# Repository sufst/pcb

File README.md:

# PCBs

## About
Central repository of all schematics and PCB design files.

| Folder     | Project                          | Project Code |
|------------|----------------------------------|--------------|
| ail        | Accumulator Indicator Light Logic| `ail`        |
| ail-led    | Accumulator Indicator Light Led  | `ail-led`    |
| batak      | Batak Game (non-car)             | `batak`      |
| break-light| Rear Break Light                 | `break-light`|
| bspd       | Brake System Plausibility Device | `bspd`       |
| can-node   | Voltage Reader and Broadcaster   | `can-node`   |
| curr-amp   | Current Sensor Amplifier         | `curr-amp`   |
| dash       | Dashboard                        | `dash`       |
| discharge  | Discharge Relay Breakout         | `discharge`  |
| hv-sense   | High Voltage Sense               | `hvs`        |
| latching   | Latch Circuit                    | `latching`   |
| loom*      | Loom Design                      | `loom`       |
| lvbms      | Low Voltage Battery Management System | `lvbms` |
| precharge  | Precharge Controller             | `precharge`  |
| segment    | Segment                          | `segment`    |
| telemetry  | On-Car Telemetry                 | `telemetry`  |
| test-rig   | PCB Test / Demo Rig              | `test`       |
| top-level* | Full Car Schematic               |              |
| trc        | TSAC Relay Controller            | `trc`        |
| tsal       | Tractive System Active Light     | `tsal`       |
| vcu        | Vehicle Control Unit             | `vcu`        |

We design our PCBs in KiCad (version 8+).

>*Moved to https://github.com/sufst/loom

## Version Control for KiCad Projects

### Why?
- Revert individual changes.
- Document development history via commits and GitHub issues.
- Easily view previous versions of designs.
- Manage shared library of components.

### Files

Files that should be in this repo, under version control:
- Project files (`.kicad_pro`).
- Schematic files (`.kicad_sch`).
- PCB files (`.kicad_pcb`).
- Custom footprints (`.kicad_mod`).
- Custom symbols (`.kicad_sym`).
- Footprint library tables (`fp-lib-table`).
- Symbol library tables (`sym-lib-table`).
- 3D models of components (`.step` files).
- Simulation code (e.g. `.asc` files from LTSpice).

Files that should never be in here:
- Exports such as BOMs, gerbers, netlists, renders, etc.
- Local project settings (`.kicad_prl`).
- Project backups (.zip files generated in `<project name>-backups`, `.bak` `.bck` `-bak` files).
- Cache files (`fp-info-cache`).

The `.gitignore` should prevent the addition of files we don't want to keep in here, but before you commit make sure to do a quick check of what is actually being added.

### Shared Resources

The `common` folder is used for resources which can be shared across multiple projects. This includes:

- Images (`images` subdirectory).
- 3D models (`step` subdirectory).
- Custom symbols (`sufst-lib.kicad_sym`).
- Custom footprints (`sufst-lib.pretty`).
- SUFST standard sheet layout (`sheet-layout.kicad_wks`).

> Note: Since projects were previously in their own individual repos, many designs still have their own libraries, step files, etc. These will gradually be migrated to the SUFST library.

### Library Paths
When you configure the library paths for a project (`sym-lib-table` and `fp-lib-table` data), make sure to always use a path relative to the project with the `${KIPRJMOD}` substitution.

- Correct: `${KIPRJMOD}/../common/sufst-lib.kicad_sym`
- Incorrect: `/Users/<your name>/Documents/sufst/pcb/common/sufst-lib.kicad_sym`

If an absolute path is used, when someone else opens the project that path will not exist and the library paths will not be valid. `-lib-table` files should never contain an absolute path.

### Git Limitations
It is not possible to resolve merge conflicts within individual design files, which is an unfortunate limitation of using `git` with KiCad. While KiCad files are in a text format, they aren't really designed to be edited manually. It is therefore *essential* that only one person is editing a particular file in a project at a time (including the shared library). Once someone starts working on a file, until it is merged into the `main` branch nobody else can edit that file. A good way to get round this is to use the "hierarchical sheets" feature to divide schematics into multiple files (if it can be done in a logical way).

## Releases

### Release Files
When a PCB is fabricated, a new 'release' for the given project should be 
created and stored within this repo in the `releases/<PROJECT NAME>` folder. 
This folder should contain the latest version (and ONLY the latest version) of
the following files:

1. Exported gerbers and drill files in a ZIP archive called `fabrication.zip`.
2. Schematic sheets as a PDF (`Schematic.pdf`).
3. Layout as a PDF in colour, with border and title block (`Layout.pdf`).
4. HTML iBOM created using the ["Interactive HTML BOM Plugin"](https://github.com/openscopeproject/InteractiveHtmlBom) (`ibom.html`).

Additionally, a file called `info` (no extension) should be created (if it 
doesn't already exist) containing release information in the following format:

```txt
version: <VERSION NUMBER>
date: <RELEASE DATE>
fabrication: <COMPANY>
```

Version numbers should be in the format `v1.0.1` and dates should be in the
format `YYYY-MM-DD`. For example:

```txt
version: v1.0.1
date: 2023-01-23
fabrication: JLCPCB
```

The release folder for a project should then have the following structure and 
file names:

```txt
<PROJECT NAME>
├── Layout.pdf
├── Schematic.pdf
├── fabrication.zip
├── ibom.html
└── info
```

When creating a new release, make sure to overwrite/replace all the existing 
files.

### Release Tag

The release commit should then be tagged with the following command:

```sh
git tag <PROJECT CODE>-<VERSION_NUMBER>
```

Tagging should be done **after** merging to `main`! Example command:

```sh
git tag segment-v1.0.1
```

To push tags to GitHub:

```sh
git push --tags
```

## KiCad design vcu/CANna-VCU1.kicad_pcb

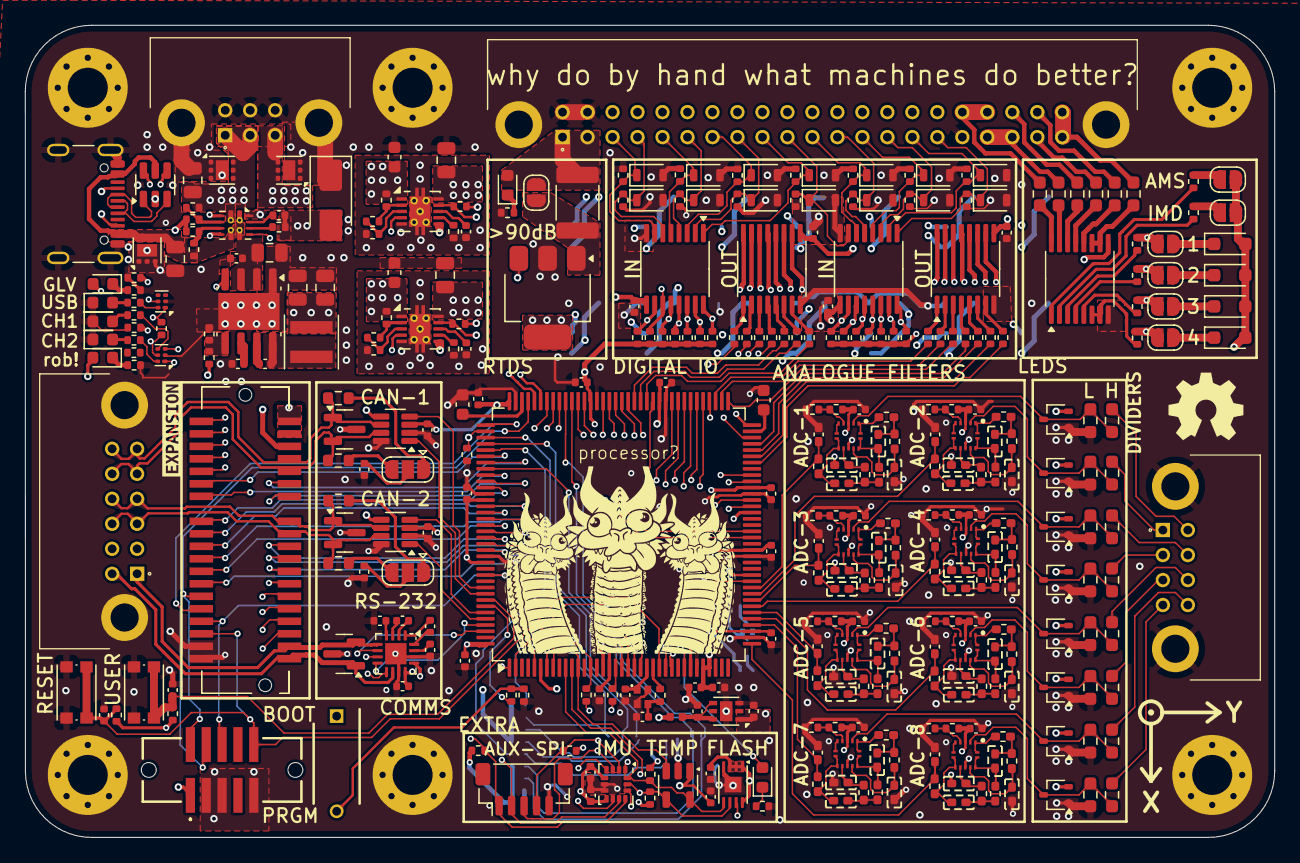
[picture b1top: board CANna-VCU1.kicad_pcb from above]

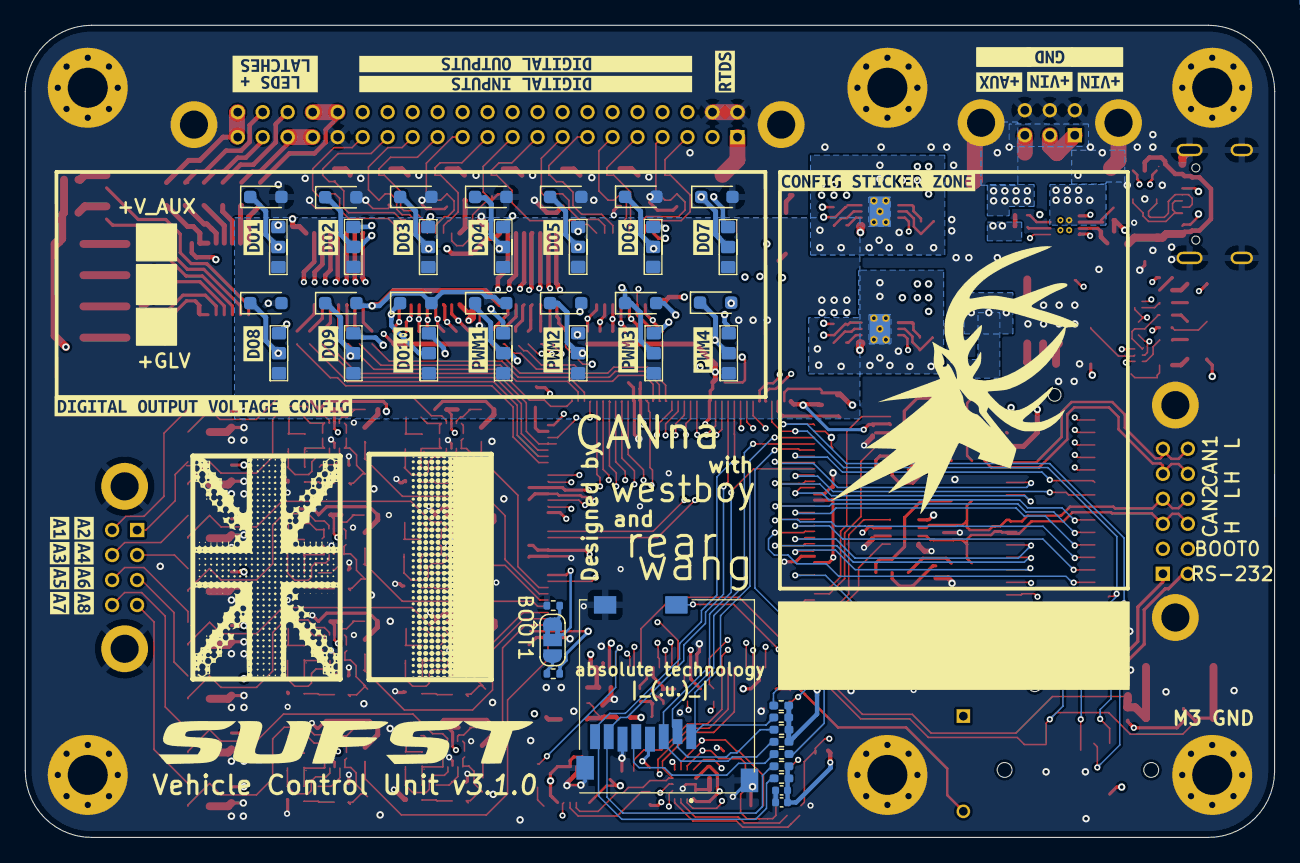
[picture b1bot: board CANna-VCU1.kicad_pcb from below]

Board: 6 copper layers, 100.0 x 65.0 mm, 442 parts (73 on the bottom side), 331 nets.

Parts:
C1, C5, C6, C8, C10, C11, C13, C14, C15, C16, C17, C19, C21, C22, C23, C31, C38, C77, C78, C79, C80, C81, C82, C83, C95, C96, C97, C98, C99, C100, C101, C104, C105, C106, C107, C108: 0.1uF; C_0402_1005Metric
C2: 10uF; C_0402_1005Metric
C3, C24, C36, C37, C39: 1uF; C_0402_1005Metric
C7, C9: 4.7pF; C_0402_1005Metric
C12: 4.7uF; C_0402_1005Metric
C18, C20: 2.2uF; C_0603_1608Metric
C25, C26, C32, C33, C34: 10uF; C_0805_2012Metric
C27, C28: 10nF; C_0402_1005Metric
C29, C30: 1uF; C_0603_1608Metric
C35: 220nF; C_0402_1005Metric
C40, C41: 22uF; C_0805_2012Metric
C42, C43, C44, C45, C46, C47, C48, C49, C50, C51, C52, C53, C54, C55, C56, C57, C58, C59, C60, C61, C62, C63, C64, C65, C66, C67, C68, C69: x; capacitor_0402_handsolder_nosilk
C70, C71, C72, C73, C74, C75, C76: x; C_0402_1005Metric_Pad0.74x0.62mm_HandSolder
C85, C89: 1nF; capacitor_0402_handsolder_nosilk
C86: 1.54nF; capacitor_0402_handsolder_nosilk
C90: 10.5nF; capacitor_0402_handsolder_nosilk
C92: 1nF; C_0402_1005Metric_Pad0.74x0.62mm_HandSolder
C102, C103: 4.7nF; C_0402_1005Metric
D1, D51: LED_BLUE; LED_0603_1608Metric
D2, D14, D33: LED_RED; LED_0603_1608Metric
D3: SS14; D_SMA
D4, D6: LED_GREEN; LED_0603_1608Metric
D7, D8, D9, D10, D11, D12, D13: BAT54SW,115; SOT-323_SC-70
D15, D16, D17, D18, D19, D20, D21, D22, D23, D24, D25, D26, D27, D28: TSD18DYFR; D_SOD-323_wide
D29, D30, D31, D32: NSR0340HT1G; D_SOD-323_HandSoldering
D34, D35, D36, D37, D38, D39, D40, D41, D42, D43, D44, D45, D46, D47: TSD18DYFR; D_SOD-323_HandSoldering
D48, D49, D50: NUP2105LT1G; SOT-23
FB1: 0; L_0402_1005Metric
H1, H2, H3, H4, H5, H6: MountingHole_Pad; MountingHole_3.2mm_M3_Pad_Via
J1: M80-5404242
J2: M80-5401242
J3: M80-5400842
J4: M80-5400642
J5: USB4105-GF-A; USB_C_Receptacle_GCT_USB4105-xx-A_16P_TopMnt_Horizontal
J6: MEC1-120-02-L-D-A-K-TR; MEC112002LDAKTR
J7: MEM2061-01-188-00-A; MEM20610118800A
J8: BM05B-SRSS-TB(LF)(SN); JST_SH_BM05B-SRSS-TB_1x05-1MP_P1.00mm_Vertical
J9: SHF-105-01-L-D-SM-LC; SHF10501LDSMLC
JP1: SolderJumper_3_Bridged12; SolderJumper-3_P1.3mm_Bridged2Bar12_RoundedPad1.0x1.5mm
JP2, JP3, JP4, JP5, JP6, JP7, JP8: SolderJumper_2_Open; SolderJumper-2_P1.3mm_Open_RoundedPad1.0x1.5mm
JP9, JP10: SolderJumper_3_Open; SolderJumper-3_P1.3mm_Open_RoundedPad1.0x1.5mm
L1: XFL4020-222MEC; L_Coilcraft_XxL4020
MP1: BAT54SW,115; SOT-323_SC-70
R1: 1k; R_0402_1005Metric_Pad0.72x0.64mm_HandSolder
R2, R3, R6, R7, R8: 47k; R_0402_1005Metric_Pad0.72x0.64mm_HandSolder
R4, R5, R32, R34: 5.1k; R_0402_1005Metric
R9: 22R; R_0402_1005Metric_Pad0.72x0.64mm_HandSolder
R10, R17, R18, R187, R188: 10k; R_0402_1005Metric
R11, R12: 47k; R_0402_1005Metric
R13, R16, R39, R41, R42, R45: 100k; R_0402_1005Metric
R14, R193: 560R; R_0402_1005Metric
R15: 1.3k; R_0402_1005Metric
R19, R20, R38, R43: 1.5k; R_0402_1005Metric
R21, R22: 2.2k; R_0402_1005Metric
R23, R180: 3k; R_0402_1005Metric
R24, R27: 300k; R_0402_1005Metric
R25, R28: 82k; R_0402_1005Metric
R26, R29: 30k; R_0402_1005Metric
R30, R35: 7.5k; R_0402_1005Metric
R31: 22k; R_0402_1005Metric
R33: 150k; R_0402_1005Metric
R37: 20k; R_0402_1005Metric
R40: 56k; R_0402_1005Metric
R46: 43.2k; R_0402_1005Metric
R49, R50, R51, R52, R53, R54, R55, R56, R57, R58, R59, R60, R61, R62: x; R_0603_1608Metric_Pad0.98x0.95mm_HandSolder
R63, R64, R65, R66, R67, R68, R69, R70, R71, R72, R73, R74, R75, R76, R77, R78, R79, R80, R81, R82, R83, R84, R85, R86, R87, R88, R89, R90, R91, R92, R93, R94, R95, R96, R97: x; R_0402_1005Metric_Pad0.72x0.64mm_HandSolder
R98, R99, R100, R101, R102, R103, R104, R105, R106, R107, R108, R109, R110, R111, R130, R131, R132, R133, R134, R135, R136, R137, R138, R139, R140, R141, R142, R143: x; R_0402_1005Metric
R112: 306k; R_0603_1608Metric_Pad0.98x0.95mm_HandSolder
R113: 214.5k; R_0603_1608Metric_Pad0.98x0.95mm_HandSolder
R116: 2.37k; R_0402_1005Metric_Pad0.72x0.64mm_HandSolder
R117: 2.8k; R_0402_1005Metric_Pad0.72x0.64mm_HandSolder
R122: 931R; R_0402_1005Metric_Pad0.72x0.64mm_HandSolder
R123: 1.05k; R_0402_1005Metric_Pad0.72x0.64mm_HandSolder
R126: 3.16k; R_0402_1005Metric_Pad0.72x0.64mm_HandSolder
R128, R129: 250k; R_0402_1005Metric
R144, R145, R146, R147, R148, R149, R150, R151, R152, R153, R154, R155, R156, R157: 1k; R_0402_1005Metric
R158, R159, R160, R161, R162, R163, R164, R165, R166, R167, R168, R169, R170, R171, R172, R174, R175, R176, R177, R178, R179: 0; R_0402_1005Metric
R173: 30; R_1812_4532Metric_Pad1.30x3.40mm_HandSolder
R181, R182, R183, R184, R185, R186: 0; R_0603_1608Metric_Pad0.98x0.95mm_HandSolder
R189, R190, R191, R192: 60R; R_0603_1608Metric
SW1, SW3: KMR241G LFS; SW_Push_1P1T_NO_CK_KMR2
SW2: A6T-1102; A6T-1101
U1: USBLC6-2SC6; SOT-23-6
U2: M24256E-FMC6TG; WFDFPN-8-1EP_3x2mm_P0.5mm_EP1.25x1.35mm
U3: ISM330DHCXTR; LGA-14_3x2.5mm_P0.5mm_LayoutBorder3x4y
U4: MCP9800A5T-M/OT; SOT-23-5
U5: STM32F746ZGT6; LQFP-144_20x20mm_P0.5mm
U6, U8: TVS1800DRVR; WSON-6-1EP_2x2mm_P0.65mm_EP1x1.6mm
U7: TVS0500DRVR; WSON-6-1EP_2x2mm_P0.65mm_EP1x1.6mm
U9, U10: TPS26625DRCR; VSON-10-1EP_3x3mm_P0.5mm_EP1.65x2.4mm_ThermalVias
U11: TPS2121RUXR; Texas_VQFN-HR-12_2x2.5mm_P0.5mm_ThermalVias
U12: NCV8730BMTW330TBG; DFN-6-1EP_2x2mm_P0.65mm_EP1x1.6mm
U13: LMR33630BDDAR; Texas_R-PDSO-G8_EP2.95x4.9mm_Mask2.4x3.1mm
U14, U15: SN74LVC2G17DRYR; Texas_USON-6_1x1.45mm_P0.5mm_SMD
U16, U17, U18, U19, U20, U21, U22, U23: TLV9104IRUCR
U25, U26, U28, U29, U30: TPL7407LPWR; TSSOP-16_4.4x5mm_P0.65mm
U27: ISP452HUMA1; SOT-223
U31, U32, U33, U34, U35, U36, U37, U38, U39, U40, U41, U42, U43, U44: SUFST_2x_Resistor_Selector_0603
U46, U47: TCAN3403DDFRQ1; SOT-23-8
U48: TRS3221EIRGTR; QFN-16-1EP_3x3mm_P0.5mm_EP1.7x1.7mm
Y1: ECS-250-10-47Q-CES-TR; Resonator_SMD_ECS_ECX-1247Q_1.6x1.2x0.3mm
kibuzzard-697BD61C: G***; kibuzzard-697BD61C
kibuzzard-6946D805: G***; kibuzzard-6946D805
kibuzzard-6946DF4F: G***; kibuzzard-6946DF4F
kibuzzard-6946DFE5: G***; kibuzzard-6946DFE5
kibuzzard-6946DFEA: G***; kibuzzard-6946DFEA
kibuzzard-6946DFF1: G***; kibuzzard-6946DFF1
kibuzzard-6946E0D2: G***; kibuzzard-6946E0D2
kibuzzard-6946E03E: G***; kibuzzard-6946E03E
kibuzzard-6946E12C: G***; kibuzzard-6946E12C
kibuzzard-6946E15A: G***; kibuzzard-6946E15A
kibuzzard-6946E16B: G***; kibuzzard-6946E16B
kibuzzard-6946E17E: G***; kibuzzard-6946E17E
kibuzzard-6946E038: G***; kibuzzard-6946E038
kibuzzard-6946E049: G***; kibuzzard-6946E049
kibuzzard-6946E137: G***; kibuzzard-6946E137
kibuzzard-6946E173: G***; kibuzzard-6946E173
kibuzzard-6955C1D0: G***; kibuzzard-6955C1D0
kibuzzard-6955C37E: G***; kibuzzard-6955C37E
kibuzzard-6955C320: G***; kibuzzard-6955C320
kibuzzard-6955C357: G***; kibuzzard-6955C357
kibuzzard-69488B9C, kibuzzard-69488B9C#2: G***; kibuzzard-69488B9C
kibuzzard-69488E03: G***; kibuzzard-69488E03
kibuzzard-694886AE: G***; kibuzzard-694886AE
kibuzzard-694896AB: G***; kibuzzard-694896AB
kibuzzard-694896B2: G***; kibuzzard-694896B2
kibuzzard-694896BE: G***; kibuzzard-694896BE
kibuzzard-694896C3: G***; kibuzzard-694896C3
kibuzzard-694896CA: G***; kibuzzard-694896CA
kibuzzard-694896CF: G***; kibuzzard-694896CF
kibuzzard-6944371B: G***; kibuzzard-6944371B
kibuzzard-69489640: G***; kibuzzard-69489640
kibuzzard-69489657: G***; kibuzzard-69489657

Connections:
+3V3: C1.2, C2.1, C5.2, C6.2, C8.1, C11.1, C12.1, C13.1, C14.1, C15.1, C16.1, C17.1, C19.1, C21.1, C22.1, C40.1, C41.1, C100.2, C101.2, C105.2, J2.8, J6.6, J7.P4 (VDD), J9.1 (VTref), L1.2, R1.2, R2.2, R3.2, R6.2, R7.2, R8.2, R10.1, R11.2, R12.2, R16.2, R21.2, R22.2, R45.2, R144.2, R145.2, R146.2, R147.2, R148.2, R149.2, R150.2, R151.2, R152.2, R153.2, R154.2, R155.2, R156.2, R157.2, R187.2, SW2.1 (A), U2.1 (E0), U2.2 (E1), U2.3 (E2), U2.8 (VCC), U3.5 (VDDIO), U3.8 (VDD), U4.1 (V_{DD}), U5.6 (VBAT), U5.17 (VDD), U5.30 (VDD), U5.39 (VDD), U5.52 (VDD), U5.62 (VDD), U5.72 (VDD), U5.84 (VDD), U5.95 (VDDUSB), U5.108 (VDD), U5.121 (VDD), U5.131 (VDD), U5.144 (VDD), U46.3 (VCC), U46.5 (SHDN), U47.3 (VCC), U47.5 (SHDN), U48.12 (VCC)
+3V3A: C23.1, C24.1, C39.1, C77.2, C78.2, C79.2, C80.2, C81.2, C82.2, C83.2, C95.2, D7.2 (K), D8.2 (K), D9.2 (K), D10.2 (K), D11.2 (K), D12.2 (K), D13.2 (K), MP1.2 (K), R37.2, R39.2, R41.2, R42.2, R98.2, R100.2, R102.2, R104.2, R106.2, R108.2, R110.2, R128.2, U5.32 (VREF+), U5.33 (VDDA), U12.1 (OUT), U14.5 (V_{CC}), U15.5 (V_{CC}), U16.3 (V+), U17.3 (V+), U18.3 (V+), U19.3 (V+), U20.3 (V+), U21.3 (V+), U22.3 (V+), U23.3 (V+)
+5V_USB: C25.1, J5.A4 (VBUS), J5.A9 (VBUS), J5.B4 (VBUS), J5.B9 (VBUS), R31.1, U1.5 (VBUS), U7.4 (IN), U7.5 (IN), U7.6 (IN), U11.7 (IN1)
+VIN: C26.1, C29.1, C96.1, C97.1, C98.2, C99.2, D2.2 (A), J4.1, J4.2, J6.2, R24.1, R33.1, U6.4 (IN), U6.5 (IN), U6.6 (IN), U9.1 (IN), U11.2 (IN2), U25.9 (VCC), U26.9 (VCC), U28.9 (VCC), U29.9 (VCC), U30.9 (COM)
+V_AUX: C30.1, J4.3, R27.1, U8.4 (IN), U8.5 (IN), U8.6 (IN), U10.1 (IN)
+V_CH1: C33.1, U9.10 (OUT), U27.4 (Vbb), U31.2, U32.2, U33.2, U34.2, U35.2, U36.2, U37.2, U38.2, U39.2, U40.2, U41.2, U42.2, U43.2, U44.2
+V_CH2: C32.1, U10.10 (OUT), U31.1, U32.1, U33.1, U34.1, U35.1, U36.1, U37.1, U38.1, U39.1, U40.1, U41.1, U42.1, U43.1, U44.1
/A1_IN: J3.5, R112.1
/A2_IN: J3.1, R52.1
/A3_IN: J3.6, R53.1
/A4_IN: J3.2, R54.1
/A5_IN: J3.7, R55.1
/A6_IN: J3.3, R49.1
/A7_IN: J3.8, R50.1
/A8_IN: J3.4, R51.1
/ADC/A1_MCU: C92.1, R126.1, U5.46 (PB0)
/ADC/A2_MCU: C73.1, R94.1, U5.45 (PC5)
/ADC/A3_MCU: C74.1, R95.1, U5.44 (PC4)
/ADC/A4_MCU: C75.1, R96.1, U5.43 (PA7)
/ADC/A5_MCU: C76.1, R97.1, U5.42 (PA6)
/ADC/A6_MCU: C70.1, R91.1, U5.41 (PA5)
/ADC/A7_MCU: C71.1, R92.1, U5.40 (PA4)
/ADC/A8_MCU: C72.1, R93.1, U5.37 (PA3)
/BOOT_SW: J2.2, R17.1, R18.2, SW2.2 (B)
/CAN1+: D48.2 (K), J2.5, J2.11, J6.10, R189.2, U46.7 (CANH)
/CAN1-: D48.1 (K), J2.6, J2.12, J6.8, R190.1, U46.6 (CANL)
/CAN2+: D49.2 (K), J2.3, J2.9, J6.20, R191.2, U47.7 (CANH)
/CAN2-: D49.1 (K), J2.4, J2.10, J6.18, R192.1, U47.6 (CANL)
/CAN/CAN1_RX: U5.135 (PB5), U46.4 (RXD)
/CAN/CAN1_TX: U5.136 (PB6), U46.1 (TXD)
/CAN/CAN2_RX: U5.139 (PB8), U47.4 (RXD)
/CAN/CAN2_TX: U5.140 (PB9), U47.1 (TXD)
/CAN/RS232_BAD: U5.5 (PE6), U48.7 (~INVALID)
/CAN/RS232_FOFF: U5.7 (PC13), U48.13 (~FORCEOFF)
/CAN/RS232_FON: U5.8 (PC14), U48.9 (FORCEON)
/CAN/UART0_RX: U5.141 (PE0), U48.8 (DIN)
/CAN/UART0_TX: U5.142 (PE1), U48.6 (ROUT)
/DI_1: D27.1 (K), J1.3, R142.1, U25.7 (A7)
/DI_2: D25.1 (K), J1.4, R140.1, U25.6 (A6)
/DI_3: D23.1 (K), J1.5, R138.1, U25.5 (A5)
/DI_4: D21.1 (K), J1.6, R136.1, U25.4 (A4)
/DI_5: D19.1 (K), J1.7, R134.1, U25.3 (A3)
/DI_6: D17.1 (K), J1.8, R132.1, U25.2 (A2)
/DI_7: D15.1 (K), J1.9, R130.1, U25.1 (A1)
/DI_8: D28.1 (K), J1.10, R143.1, U26.7 (A7)
/DI_9: D26.1 (K), J1.11, R141.1, U26.6 (A6)
/DI_10: D24.1 (K), J1.12, R139.1, U26.5 (A5)
/DI_11: D22.1 (K), J1.13, R137.1, U26.4 (A4)
/DI_12: D20.1 (K), J1.14, R135.1, U26.3 (A3)
/DI_13: D18.1 (K), J1.15, R133.1, U26.2 (A2)
/DI_14: D16.1 (K), J1.16, R131.1, U26.1 (A1)
/DO_1: D34.1 (K), J1.37, U29.10 (Y7), U32.3
/DO_2: D36.1 (K), J1.36, U29.11 (Y6), U34.3
/DO_3: D38.1 (K), J1.35, U29.12 (Y5), U36.3
/DO_4: D40.1 (K), J1.34, U29.13 (Y4), U38.3
/DO_5: D42.1 (K), J1.33, U29.14 (Y3), U40.3
/DO_6: D44.1 (K), J1.32, U29.15 (Y2), U42.3
/DO_7: D46.1 (K), J1.31, U29.16 (Y1), U44.3
/DO_8: D35.1 (K), J1.30, U28.10 (Y7), U31.3
/DO_9: D37.1 (K), J1.29, U28.11 (Y6), U33.3
/DO_10: D39.1 (K), J1.28, U28.12 (Y5), U35.3
/HSIO/CHECK_LED: D29.2 (A), D30.2 (A), D31.2 (A), D32.2 (A), JP2.1 (A), JP3.1 (A), U5.58 (PE7)
/HSIO/LATCH_1: R181.1, U30.16 (OUT1)
/HSIO/LATCH_2: R182.1, U30.15 (OUT2)
/HSIO/LSDI_1: R157.1, U5.97 (PC7), U25.10 (Y7)
/HSIO/LSDI_2: R155.1, U5.96 (PC6), U25.11 (Y6)
/HSIO/LSDI_3: R153.1, U5.93 (PG8), U25.12 (Y5)
/HSIO/LSDI_4: R151.1, U5.92 (PG7), U25.13 (Y4)
/HSIO/LSDI_5: R149.1, U5.91 (PG6), U25.14 (Y3)
/HSIO/LSDI_6: R147.1, U5.90 (PG5), U25.15 (Y2)
/HSIO/LSDI_7: R145.1, U5.89 (PG4), U25.16 (Y1)
/HSIO/LSDI_8: R156.1, U5.85 (PD14), U26.10 (Y7)
/HSIO/LSDI_9: R154.1, U5.82 (PD13), U26.11 (Y6)
/HSIO/LSDI_10: R152.1, U5.81 (PD12), U26.12 (Y5)
/HSIO/LSDI_11: R150.1, U5.80 (PD11), U26.13 (Y4)
/HSIO/LSDI_12: R148.1, U5.79 (PD10), U26.14 (Y3)
/HSIO/LSDI_13: R146.1, U5.78 (PD9), U26.15 (Y2)
/HSIO/LSDI_14: R144.1, U5.77 (PD8), U26.16 (Y1)
/HSIO/LSDO_1: R172.2, U5.66 (PE13)
/HSIO/LSDO_2: R171.2, U5.67 (PE14)
/HSIO/LSDO_3: R170.2, U5.68 (PE15)
/HSIO/LSDO_4: R169.2, U5.69 (PB10)
/HSIO/LSDO_5: R168.2, U5.73 (PB12)
/HSIO/LSDO_6: R167.2, U5.74 (PB13)
/HSIO/LSDO_7: R166.2, U5.75 (PB14)
/HSIO/LSDO_8: R165.2, U5.86 (PD15)
/HSIO/LSDO_9: R164.2, U5.87 (PG2)
/HSIO/LSDO_10: R163.2, U5.88 (PG3)
/HSIO/LSDO_PWM1: R162.2, U5.70 (PB11)
/HSIO/LSDO_PWM2: R161.2, U5.76 (PB15)
/HSIO/LSDO_PWM3: R160.2, U5.47 (PB1)
/HSIO/LSDO_PWM4: R159.2, U5.19 (PF7)
/HSIO/LSD_RTDS: R158.1, U5.18 (PF6)
/HSIO/LS_LED_1: JP4.2 (B), R176.2, U5.64 (PE11)
/HSIO/LS_LED_2: JP5.2 (B), R177.2, U5.63 (PE10)
/HSIO/LS_LED_3: JP6.2 (B), R178.2, U5.60 (PE9)
/HSIO/LS_LED_4: JP7.2 (B), R179.2, U5.59 (PE8)
/LATCH_1: J1.38, J1.39, R181.2
/LATCH_2: J1.18, J1.19, R182.2
/LS_LED_1: J1.40, R183.2
/LS_LED_2: J1.20, R184.2
/LS_LED_3: J1.41, R185.2
/LS_LED_4: J1.21, J1.42, R186.2
/MCU/AUX_ENAB: J6.34, J8.2, U3.10 (OCS_AUX)
/MCU/AUX_SCK: J6.32, J8.3, U3.3 (SCx)
/MCU/AUX_SDI: J6.30, J8.4, R11.1, U3.2 (SDx)
/MCU/AUX_SDO: J6.36, J8.1, R12.1, U3.11 (SDO_AUX)
/MCU/BOOT0: R18.1, U5.138 (BOOT0)
/MCU/BOOT1: JP1.2 (C), U5.48 (PB2)
/MCU/EEPROM_WC: U2.7 (WC), U5.27 (PC1)
/MCU/I2C0_SCL: R22.1, U2.6 (SCL), U3.13 (SCL), U4.4 (SCLK), U5.11 (PF1)
/MCU/I2C0_SDA: R21.1, U2.5 (SDA), U3.14 (SDA), U4.5 (SDA), U5.10 (PF0)
/MCU/I2C1_SCL: J6.3, U5.54 (PF14)
/MCU/I2C1_SDA: J6.1, U5.55 (PF15)
/MCU/IMU_ADDR: U3.1 (SDO/SA0), U5.22 (PF10)
/MCU/IMU_INTR1: U3.4 (INT1), U5.20 (PF8)
/MCU/IMU_INTR2: U3.9 (INT2), U5.21 (PF9)
/MCU/IMU_MODE: U3.12 (CS), U5.26 (PC0)
/MCU/OSC_IN: C9.1, U5.23 (PH0), Y1.1
/MCU/OSC_OUT: R15.1, U5.24 (PH1)
/MCU/PG_3V3: R42.1, U5.14 (PF4), U13.4 (PG)
/MCU/SD_CARD_DETECT: J7.CD1 (DET_A), R1.1, U5.2 (PE3)
/MCU/SD_CK: R9.2, U5.113 (PC12)
/MCU/SD_CMD: J7.P3 (CMD), R8.1, U5.116 (PD2)
/MCU/SD_D0: J7.P7 (DAT0), R2.1, U5.98 (PC8)
/MCU/SD_D1: J7.P8 (DAT1), R3.1, U5.99 (PC9)
/MCU/SD_D2: J7.P1 (DAT2), R6.1, U5.111 (PC10)
/MCU/SD_D3: J7.P2 (DAT3/CD), R7.1, U5.112 (PC11)
/MCU/SPI_MISO: J6.22, U5.127 (PG12)
/MCU/SPI_MOSI: J6.26, U5.129 (PG14)
/MCU/SPI_SCK: J6.24, U5.128 (PG13)
/MCU/SWCLK: J6.31, J9.4 (SWCLK/TCK), U5.109 (PA14)
/MCU/SWDIO: J6.29, J9.2 (SWDIO/TMS), U5.105 (PA13)
/MCU/SWO: J6.33, J9.6 (SWO/TDO), U5.133 (PB3)
/MCU/TOO_HOT: J6.28, U4.3 (ALERT), U5.12 (PF2)
/MCU/USART1_CK: J6.5, U5.100 (PA8)
/MCU/USART1_RX: J6.9, U5.102 (PA10)
/MCU/USART1_TX: J6.7, U5.101 (PA9)
/MCU/USB_D+: U1.4 (I/O2), U5.104 (PA12)
/MCU/USB_D-: U1.6 (I/O1), U5.103 (PA11)
/MCU/USB_UN_D+: J5.A6 (D+), J5.B6 (D+), U1.3 (I/O2)
/MCU/USB_UN_D-: J5.A7 (D-), J5.B7 (D-), U1.1 (I/O1)
/MCU/XP_GP_1: J6.11, U5.114 (PD0)
/MCU/XP_GP_2: J6.12, U5.115 (PD1)
/MCU/XP_GP_3: J6.13, U5.117 (PD3)
/MCU/XP_GP_4: J6.14, U5.118 (PD4)
/MCU/XP_GP_5: J6.17, U5.119 (PD5)
/MCU/XP_GP_6: J6.19, U5.122 (PD6)
/MCU/XP_GP_7: J6.21, U5.123 (PD7)
/MCU/XP_GP_8: J6.23, U5.124 (PG9)
/MCU/XP_GP_9: J6.25, U5.125 (PG10)
/MCU/XP_GP_10: J6.27, U5.126 (PG11)
/MCU/button: C3.2, R10.2, SW1.1, U5.137 (PB7)
/MCU/nRST: C10.2, J6.35, J9.10 (~RESET), R16.1, SW3.1, U5.25 (NRST)
/MCU/rob_led!: D1.2 (A), U5.1 (PE2)
/MCU/spare_led: D51.2 (A), U5.29 (PC3)
/MCU/~KILL: R13.2, U5.110 (PA15), U9.4 (~(SHDN)), U10.4 (~(SHDN))
/PWM1: D41.1 (K), J1.27, U28.13 (Y4), U37.3
/PWM2: D43.1 (K), J1.26, U28.14 (Y3), U39.3
/PWM3: D45.1 (K), J1.25, U28.15 (Y2), U41.3
/PWM4: D47.1 (K), J1.24, U28.16 (Y1), U43.3
/Power/FB1: R45.1, R46.2, U13.5 (FB)
/Power/MUX: R37.1, U11.9 (ST), U15.1 (1A)
/Power/SW: C38.2, L1.1, U13.8 (SW)
/Power/~FAULT_CH1: R39.1, U9.9 (~(FLT)), U14.3 (2A)
/Power/~FAULT_CH2: R41.1, U10.9 (~(FLT)), U14.1 (1A)
/RS232_RX: D50.2 (K), J2.1, J6.38, U48.5 (RIN)
/RS232_TX: D50.1 (K), J2.7, J6.40, U48.10 (DOUT)
/RTDS+: D33.2 (A), J1.1, J1.2, JP8.1 (A), R173.2
GND: C1.1, C2.2, C3.1, C5.1, C6.1, C7.2, C8.2, C9.2, C10.1, C11.2, C12.2, C13.2, C14.2, C15.2, C16.2, C17.2, C18.1, C19.2, C20.1, C21.2, C22.2, C23.2, C24.2, C25.2, C26.2, C29.2, C30.2, C32.2, C33.2, C34.2, C35.2, C36.2, C37.2, C39.2, C40.2, C41.2, C42.2, C43.2, C44.2, C45.2, C46.2, C47.2, C48.2, C56.2, C57.2, C58.2, C59.2, C60.2, C61.2, C62.2, C70.2, C71.2, C72.2, C73.2, C74.2, C75.2, C76.2, C77.1, C78.1, C79.1, C80.1, C81.1, C82.1, C83.1, C85.2, C89.2, C92.2, C95.1, C96.2, C97.2, C98.1, C99.1, C100.1, C101.1, C102.2, C103.2, C105.1, C107.2, C108.2, D3.1 (K), D4.1 (K), D6.1 (K), D7.1 (A), D8.1 (A), D9.1 (A), D10.1 (A), D11.1 (A), D12.1 (A), D13.1 (A), D14.1 (K), D15.2 (A), D16.2 (A), D17.2 (A), D18.2 (A), D19.2 (A), D20.2 (A), D21.2 (A), D22.2 (A), D23.2 (A), D24.2 (A), D25.2 (A), D26.2 (A), D27.2 (A), D28.2 (A), D34.2 (A), D35.2 (A), D36.2 (A), D37.2 (A), D38.2 (A), D39.2 (A), D40.2 (A), D41.2 (A), D42.2 (A), D43.2 (A), D44.2 (A), D45.2 (A), D46.2 (A), D47.2 (A), D48.3 (A), D49.3 (A), D50.3 (A), H1.1, H2.1, H3.1, H4.1, H5.1, H6.1, J1.17, J1.22, J1.23, J1.43, J1.44, J2.13, J2.14, J3.9, J3.10, J4.4, J4.5, J4.6, J4.7, J4.8, J5.A1 (GND), J5.A12 (GND), J5.B1 (GND), J5.B12 (GND), J5.S1 (SHIELD), J6.37, J6.39, J7.CD2 (DET_B), J7.G1 (SHIELD), J7.G2 (SHIELD), J7.P6 (VSS), J8.5, J9.3 (GND), J9.5 (GND), J9.9 (GNDDetect), MP1.1 (A), R4.1, R5.1, R13.1, R14.2, R17.2, R23.1, R46.1, R56.1, R57.1, R58.1, R59.1, R60.1, R61.1, R62.1, R99.1, R101.1, R103.1, R105.1, R107.1, R109.1, R111.1, R113.1, R129.1, R130.2, R131.2, R132.2, R133.2, R134.2, R135.2, R136.2, R137.2, R138.2, R139.2, R140.2, R141.2, R142.2, R143.2, R180.1, R188.2, R193.2, SW1.2, SW3.2, U1.2 (GND), U2.4 (VSS), U2.9 (EX), U3.6 (GND), U3.7 (GND), U4.2 (GND), U5.16 (VSS), U5.31 (VSSA), U5.38 (VSS), U5.51 (VSS), U5.61 (VSS), U5.83 (VSS), U5.94 (VSS), U5.107 (VSS), U5.120 (VSS), U5.130 (VSS), U6.1 (GND), U6.2 (GND), U6.3 (GND), U6.7 (GND), U7.1 (GND), U7.2 (GND), U7.3 (GND), U7.7 (GND), U8.1 (GND), U8.2 (GND), U8.3 (GND), U8.7 (GND), U9.6 (GND), U10.6 (GND), U12.3 (GND), U12.7 (EX), U13.1 (PGND), U13.9 (AGND), U14.2 (GND), U15.2 (GND), U16.10 (V-), U17.10 (V-), U18.10 (V-), U19.10 (V-), U20.10 (V-), U21.10 (V-), U22.10 (V-), U23.10 (V-), U25.8 (GND), U26.8 (GND), U27.2 (GND), U28.8 (GND), U29.8 (GND), U30.8 (GND), U46.2 (GND), U46.8 (STB), U47.2 (GND), U47.8 (STB), U48.11 (GND), U48.14 (~EN), U48.17 (XP), Y1.2, Y1.4
MGND: C31.2, D3.2 (A), R32.2, R34.2, R40.2, U11.3 (CP2), U11.6 (PR1), U11.12 (GND)
unnamed: C7.1, R15.2, Y1.3
unnamed: C49.2, R63.2, R70.1
unnamed: C50.2, R64.2, R71.1
unnamed: C51.2, R65.2, R72.1
unnamed: C52.2, R66.2, R73.1
unnamed: C53.2, R67.2, R74.1
unnamed: C54.2, R68.2, R75.1
unnamed: C55.2, R69.2, R76.1
unnamed: C63.2, R77.2, R84.1
unnamed: C64.2, R78.2, R85.1
unnamed: C65.2, R79.2, R86.1
unnamed: C66.2, R80.2, R87.1
unnamed: C67.2, R81.2, R88.1
unnamed: C68.2, R82.2, R89.1
unnamed: C69.2, R83.2, R90.1
unnamed: C86.2, R116.2, R117.1
unnamed: C90.2, R122.2, R123.1
unnamed: D1.1 (K), R14.1
unnamed: D2.1 (K), R23.2
unnamed: D4.2 (A), R38.1
unnamed: D6.2 (A), R19.1
unnamed: D7.3 (COM), R49.2, R56.2, U16.2 (+)
unnamed: D8.3 (COM), R51.2, R58.2, U18.2 (+)
unnamed: D9.3 (COM), R50.2, R57.2, U17.2 (+)
unnamed: D10.3 (COM), R53.2, R60.2, U20.2 (+)
unnamed: D11.3 (COM), R54.2, R61.2, U21.2 (+)
unnamed: D12.3 (COM), R55.2, R62.2, U22.2 (+)
unnamed: D13.3 (COM), R112.2, R113.2, U23.2 (+)
unnamed: D14.2 (A), R20.1
unnamed: D29.1 (K), JP5.1 (A)
unnamed: D30.1 (K), JP6.1 (A)
unnamed: D31.1 (K), JP7.1 (A)
unnamed: D32.1 (K), JP4.1 (A)
unnamed: D33.1 (K), R180.2
unnamed: D51.1 (K), R193.1
unnamed: J5.A5 (CC1), R4.2
unnamed: J5.B5 (CC2), R5.2
unnamed: J7.P5 (CLK), R9.1
unnamed: JP1.1 (A), R188.1
unnamed: JP1.3 (B), R187.1
unnamed: JP2.2 (B), R174.2
unnamed: JP3.2 (B), R175.2
unnamed: JP8.2 (B), R173.1, U27.1 (OUT)
unnamed: JP9.1 (A), R190.2
unnamed: JP9.3 (B), R189.1
unnamed: C102.1, JP9.2 (C)
unnamed: JP10.1 (A), R192.2
unnamed: JP10.3 (B), R191.1
unnamed: C103.1, JP10.2 (C)
unnamed: MP1.3 (COM), R52.2, R59.2, U19.2 (+)
unnamed: C18.2, U5.71 (VCAP_1)
unnamed: C20.2, U5.106 (VCAP_2)
unnamed: R30.1, U9.7 (ILIM)
unnamed: R25.2, R26.1, U9.3 (OVP)
unnamed: R24.2, R25.1, U9.2 (UVLO)
unnamed: C27.1, U9.8 (dVdT)
unnamed: R35.1, U10.7 (ILIM)
unnamed: R28.2, R29.1, U10.3 (OVP)
unnamed: R27.2, R28.1, U10.2 (UVLO)
unnamed: C28.1, U10.8 (dVdT)
unnamed: R40.1, U11.10 (ILM)
unnamed: R31.2, R32.1, U11.5 (OV1)
unnamed: R33.2, R34.1, U11.4 (OV2)
unnamed: C31.1, U11.11 (SS)
unnamed: C36.1, FB1.2, U12.4 (EN), U12.6 (IN)
unnamed: C38.1, U13.7 (BOOT)
unnamed: C34.1, C35.1, FB1.1, U11.1 (OUT), U11.8 (OUT), U13.2 (VIN), U13.3 (EN)
unnamed: C37.1, U13.6 (VCC)
unnamed: R38.2, U14.6 (1Y)
unnamed: R19.2, U14.4 (2Y)
unnamed: R20.2, U15.6 (1Y)
unnamed: R63.1, U16.1 (-), U16.14
unnamed: R106.1, R107.2, U16.4 (+)
unnamed: U16.5 (-), U16.6
unnamed: C56.1, R84.2, U16.9 (+)
unnamed: C63.1, R91.2, U16.7, U16.8 (-)
unnamed: C42.1, R70.2, U16.11 (+)
unnamed: C49.1, R77.1, U16.12 (-), U16.13
unnamed: R64.1, U17.1 (-), U17.14
unnamed: R108.1, R109.2, U17.4 (+)
unnamed: U17.5 (-), U17.6
unnamed: C57.1, R85.2, U17.9 (+)
unnamed: C64.1, R92.2, U17.7, U17.8 (-)
unnamed: C43.1, R71.2, U17.11 (+)
unnamed: C50.1, R78.1, U17.12 (-), U17.13
unnamed: R65.1, U18.1 (-), U18.14
unnamed: R110.1, R111.2, U18.4 (+)
unnamed: U18.5 (-), U18.6
unnamed: C58.1, R86.2, U18.9 (+)
unnamed: C65.1, R93.2, U18.7, U18.8 (-)
unnamed: C44.1, R72.2, U18.11 (+)
unnamed: C51.1, R79.1, U18.12 (-), U18.13
unnamed: R66.1, U19.1 (-), U19.14
unnamed: R98.1, R99.2, U19.4 (+)
unnamed: U19.5 (-), U19.6
unnamed: C59.1, R87.2, U19.9 (+)
unnamed: C66.1, R94.2, U19.7, U19.8 (-)
unnamed: C45.1, R73.2, U19.11 (+)
unnamed: C52.1, R80.1, U19.12 (-), U19.13
unnamed: R67.1, U20.1 (-), U20.14
unnamed: R100.1, R101.2, U20.4 (+)
unnamed: U20.5 (-), U20.6
unnamed: C60.1, R88.2, U20.9 (+)
unnamed: C67.1, R95.2, U20.7, U20.8 (-)
unnamed: C46.1, R74.2, U20.11 (+)
unnamed: C53.1, R81.1, U20.12 (-), U20.13
unnamed: R68.1, U21.1 (-), U21.14
unnamed: R102.1, R103.2, U21.4 (+)
unnamed: U21.5 (-), U21.6
unnamed: C61.1, R89.2, U21.9 (+)
unnamed: C68.1, R96.2, U21.7, U21.8 (-)
unnamed: C47.1, R75.2, U21.11 (+)
unnamed: C54.1, R82.1, U21.12 (-), U21.13
unnamed: R69.1, U22.1 (-), U22.14
unnamed: R104.1, R105.2, U22.4 (+)
unnamed: U22.5 (-), U22.6
unnamed: C62.1, R90.2, U22.9 (+)
unnamed: C69.1, R97.2, U22.7, U22.8 (-)
unnamed: C48.1, R76.2, U22.11 (+)
unnamed: C55.1, R83.1, U22.12 (-), U22.13
unnamed: R116.1, U23.1 (-), U23.14
unnamed: R128.1, R129.2, U23.4 (+)
unnamed: U23.5 (-), U23.6
unnamed: C89.1, R123.2, U23.9 (+)
unnamed: C90.1, R126.2, U23.7, U23.8 (-)
unnamed: C85.1, R117.2, U23.11 (+)
unnamed: C86.1, R122.1, U23.12 (-), U23.13
unnamed: R158.2, U27.3 (IN)
unnamed: R159.1, U28.1 (A1)
unnamed: R160.1, U28.2 (A2)
unnamed: R161.1, U28.3 (A3)
unnamed: R162.1, U28.4 (A4)
unnamed: R163.1, U28.5 (A5)
unnamed: R164.1, U28.6 (A6)
unnamed: R165.1, U28.7 (A7)
unnamed: R166.1, U29.1 (A1)
unnamed: R167.1, U29.2 (A2)
unnamed: R168.1, U29.3 (A3)
unnamed: R169.1, U29.4 (A4)
unnamed: R170.1, U29.5 (A5)
unnamed: R171.1, U29.6 (A6)
unnamed: R172.1, U29.7 (A7)
unnamed: R174.1, U30.1 (IN1)
unnamed: R175.1, U30.2 (IN2)
unnamed: R176.1, U30.3 (IN3)
unnamed: R177.1, U30.4 (IN4)
unnamed: R178.1, U30.5 (IN5)
unnamed: R179.1, U30.6 (IN6), U30.7 (IN7)
unnamed: R183.1, U30.14 (OUT3)
unnamed: R184.1, U30.13 (OUT4)
unnamed: R185.1, U30.12 (OUT5)
unnamed: R186.1, U30.10 (OUT7), U30.11 (OUT6)
unnamed: C106.1, U48.16 (C1+)
unnamed: C106.2, U48.1 (C1-)
unnamed: C104.2, U48.2 (C2+)
unnamed: C104.1, U48.3 (C2-)
unnamed: C107.1, U48.15 (V+)
unnamed: C108.1, U48.4 (V-)
RTN1: C27.2, R26.2, R30.2, U9.5 (RTN), U9.11 (EXP)
RTN2: C28.2, R29.2, R35.2, U10.5 (RTN), U10.11 (EXP)

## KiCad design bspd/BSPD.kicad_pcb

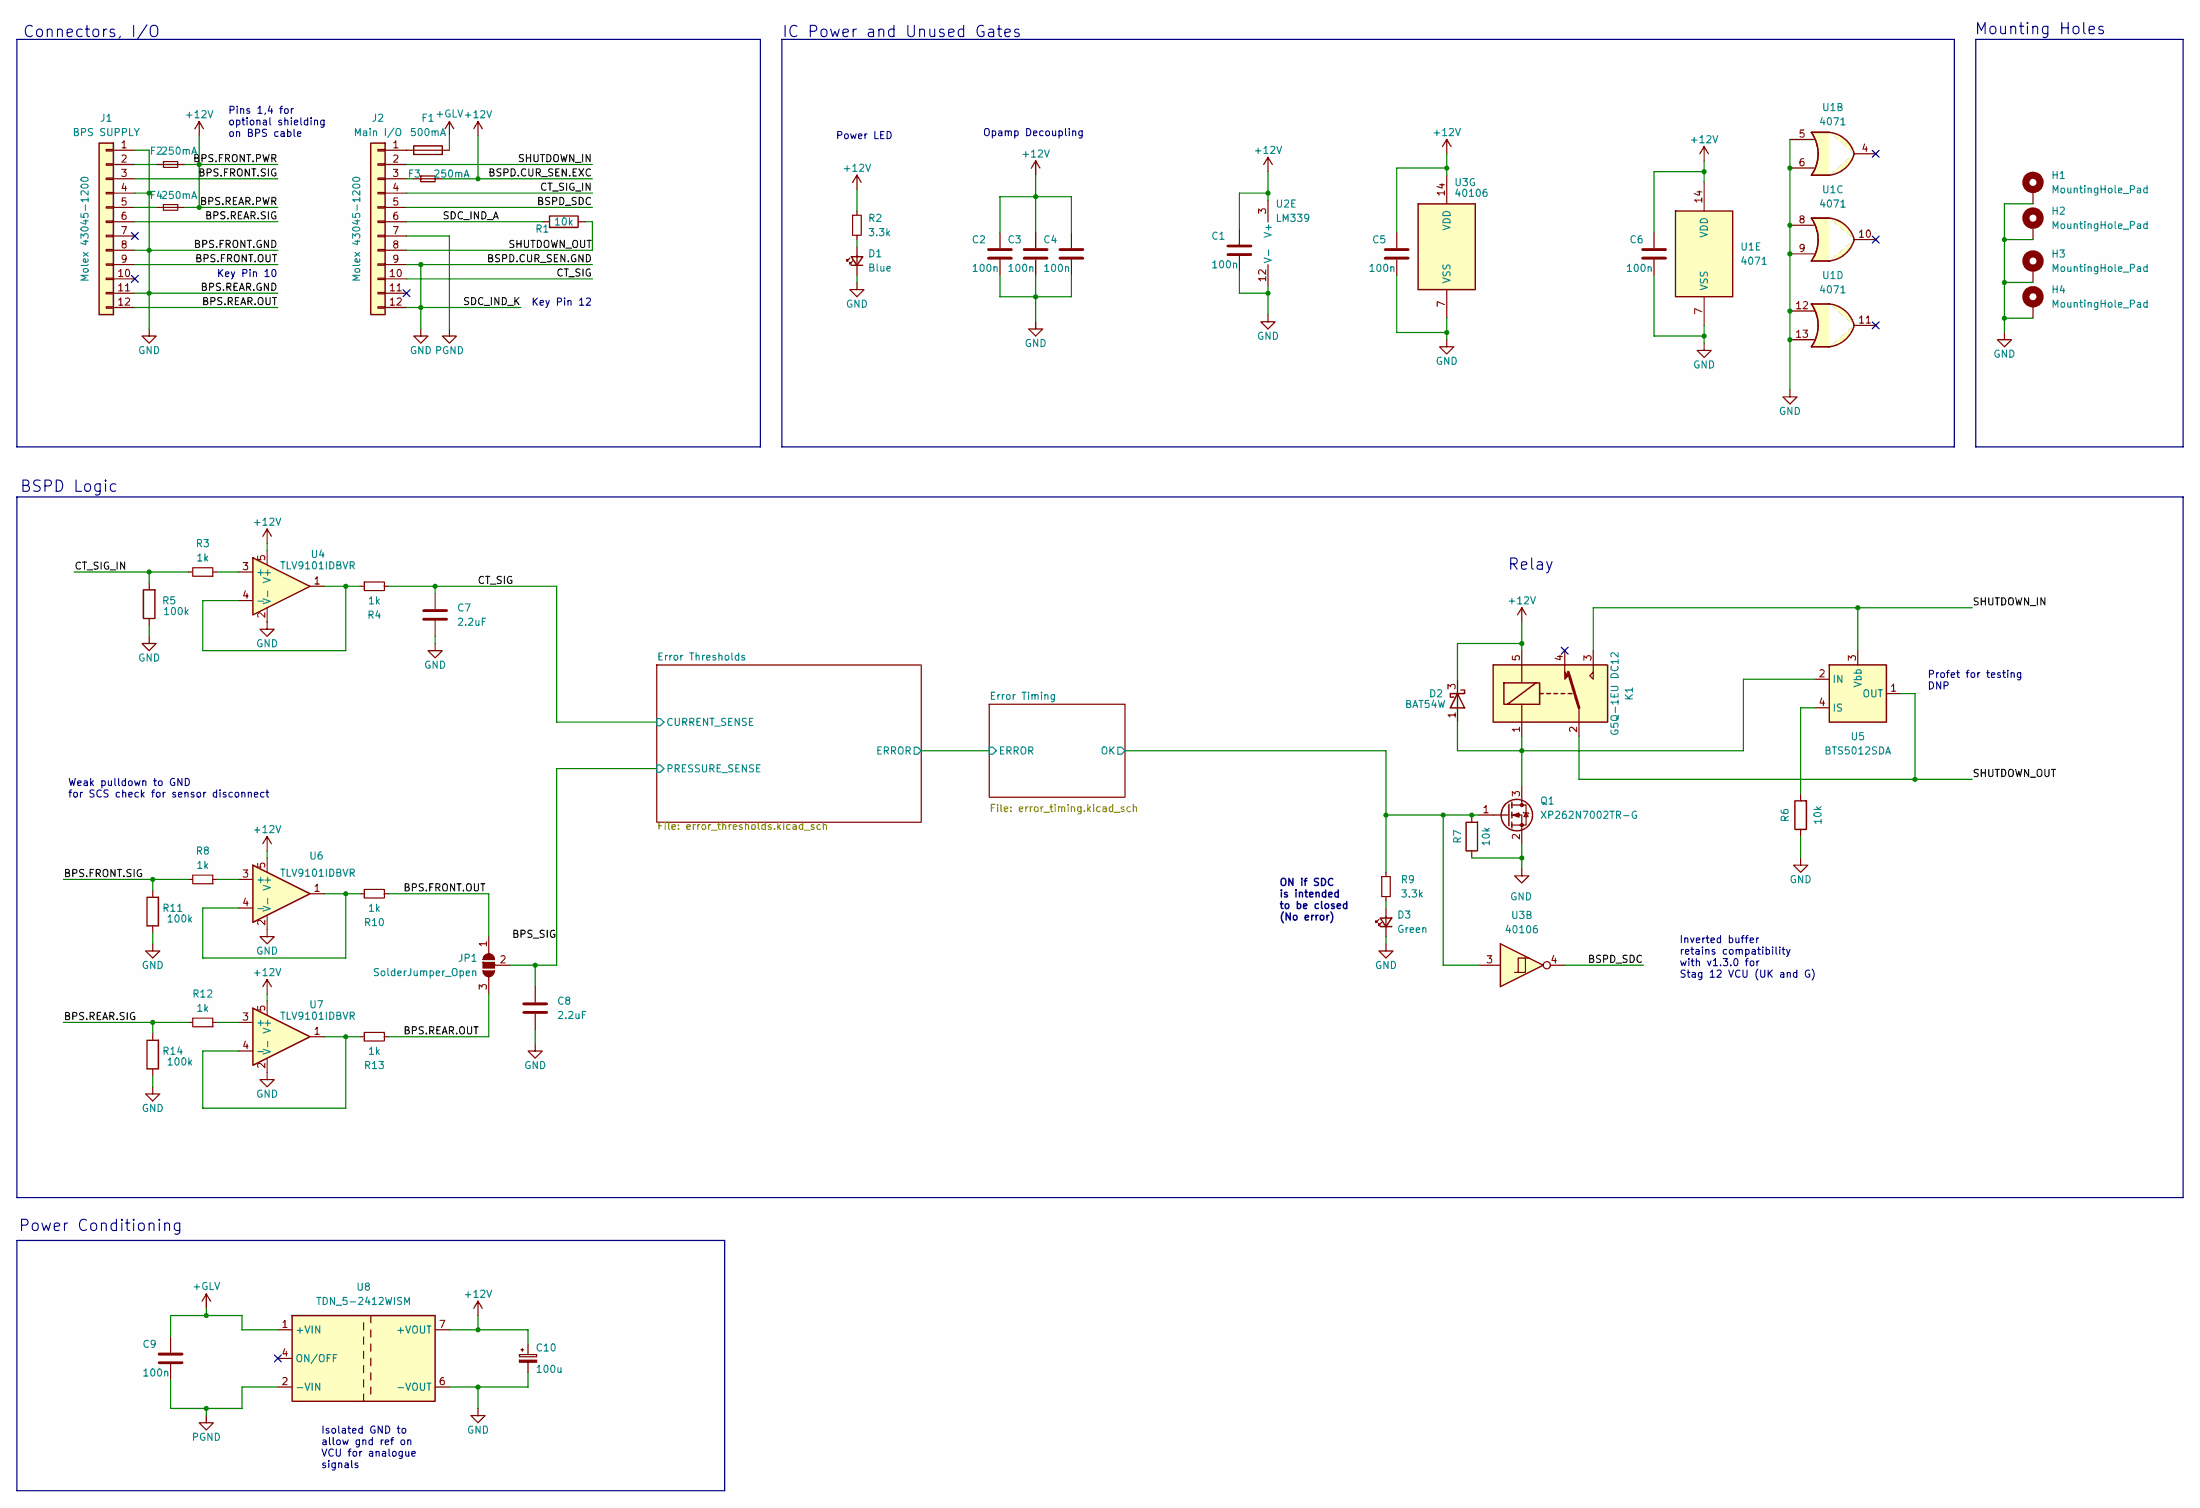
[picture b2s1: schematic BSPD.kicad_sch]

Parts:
C1, C2, C3, C4, C5, C6, C9: 100n; C_0603_1608Metric
C7, C8: 2.2uF; C_0603_1608Metric
C10: 100u; CP_Radial_D5.0mm_P2.00mm
D1: Blue; LED_0603_1608Metric
D2: BAT54W; SOT-323_SC-70
D3: Green; LED_0603_1608Metric
F1: 500mA; Fuse_0603_1608Metric
F2, F3, F4: 250mA; Fuse_0603_1608Metric
H1, H2, H3, H4: MountingHole_Pad; MountingHole_3.2mm_M3_DIN965_Pad
J1: BPS SUPPLY; Molex_Micro-Fit_3.0_43045-1200_2x06_P3.00mm_Horizontal
J2: Main I/O; Molex_Micro-Fit_3.0_43045-1200_2x06_P3.00mm_Horizontal
JP1: SolderJumper_Open; SolderJumper-3_P1.3mm_Open_RoundedPad1.0x1.5mm
K1: G5Q-1EU DC12; Relay_SPDT_Omron-G5Q-1
Q1: XP262N7002TR-G; SOT-23
R1, R6, R7: 10k; R_0603_1608Metric
R2, R9: 3.3k; R_0603_1608Metric
R3, R4, R8, R10, R12, R13: 1k; R_0603_1608Metric
R5, R11, R14: 100k; R_0603_1608Metric
U1: 4071; SOIC-14_3.9x8.7mm_P1.27mm
U2: LM339; SOIC-14_3.9x8.7mm_P1.27mm
U3: 40106; SOIC-14_3.9x8.7mm_P1.27mm
U4, U6, U7: TLV9101IDBVR; SOT-23-5_HandSoldering
U5: BTS5012SDA; TO-252-4
U8: TDN_5-2412WISM; Converter_DCDC_TRACO_TDN_5-xxxxWISM_SMD

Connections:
+12V: C1.1, C2.1, C3.1, C4.1, C5.1, C6.1, C10.1, D2.3 (K), F2.2, F3.2, F4.2, K1.5, R2.1, U1.14 (VDD), U2.3 (V+), U3.14 (VDD), U4.5 (V+), U6.5 (V+), U7.5 (V+), U8.7 (+VOUT); also elsewhere on the board
+GLV: C9.1, F1.2, U8.1 (+VIN)
/BPS.FRONT.OUT: J1.9, JP1.1 (A), R10.2
/BPS.FRONT.SIG: J1.3, R8.2, R11.2
/BPS.REAR.OUT: J1.12, JP1.3 (B), R13.2
/BPS.REAR.SIG: J1.6, R12.2, R14.2
/BPS_SIG: C8.1, JP1.2 (C); also elsewhere on the board
/BSPD_SDC: J2.5, U3.4
/CT_SIG: C7.1, J2.10, R4.2; also elsewhere on the board
/CT_SIG_IN: J2.4, R3.2, R5.2
/Error Timing/OK: Q1.1 (G), R7.2, R9.1, U3.3; also elsewhere on the board
/SDC_IND_A: J2.6, R1.2
/SHUTDOWN_IN: J2.2, K1.3, U5.3 (Vbb)
/SHUTDOWN_OUT: J2.8, K1.2, R1.1, U5.1 (OUT), U5.5 (OUT)
GND: C1.2, C2.2, C3.2, C4.2, C5.2, C6.2, C7.2, C8.2, C10.2, D1.1 (K), D3.1 (K), H1.1, H2.1, H3.1, H4.1, J1.1, J1.4, J1.8, J1.11, J2.9, J2.12, Q1.2 (S), R5.1, R6.1, R7.1, R11.1, R14.1, U1.5, U1.6, U1.7 (VSS), U1.8, U1.9, U1.12, U1.13, U2.12 (V-), U3.7 (VSS), U4.2 (V-), U6.2 (V-), U7.2 (V-), U8.6 (-VOUT); also elsewhere on the board
unnamed: D1.2 (A), R2.2
unnamed: D2.1 (A), K1.1, Q1.3 (D), U5.2 (IN)
unnamed: D3.2 (A), R9.2
unnamed: F2.1, J1.2
unnamed: F4.1, J1.5
unnamed: F1.1, J2.1
unnamed: F3.1, J2.3
unnamed: R3.1, U4.3 (+)
unnamed: R4.1, U4.1, U4.4 (-)
unnamed: R6.2, U5.4 (IS)
unnamed: R8.1, U6.3 (+)
unnamed: R10.1, U6.1, U6.4 (-)
unnamed: R12.1, U7.3 (+)
unnamed: R13.1, U7.1, U7.4 (-)
PGND: C9.2, J2.7, U8.2 (-VIN)

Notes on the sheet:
ON if SDC is intended to be closed (No error)
Key Pin 12
Profet for testing DNP
Power LED
Connectors, I/O
Inverted buffer retains compatibility with v1.3.0 for Stag 12 VCU (UK and G)
Isolated GND to allow gnd ref on VCU for analogue signals
Mounting Holes
IC Power and Unused Gates
BSPD Logic
Power Conditioning
Relay
Opamp Decoupling
Key Pin 10
Pins 1,4 for optional shielding on BPS cable
Weak pulldown to GND for SCS check for sensor disconnect
